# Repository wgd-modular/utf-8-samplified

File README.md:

# utf-8-samplified

An Arduino nano sample based 8-channel drum module for the eurorack format.

For more information on the project take a look into the [wiki](https://github.com/wgd-modular/utf-8-samplified/wiki)!

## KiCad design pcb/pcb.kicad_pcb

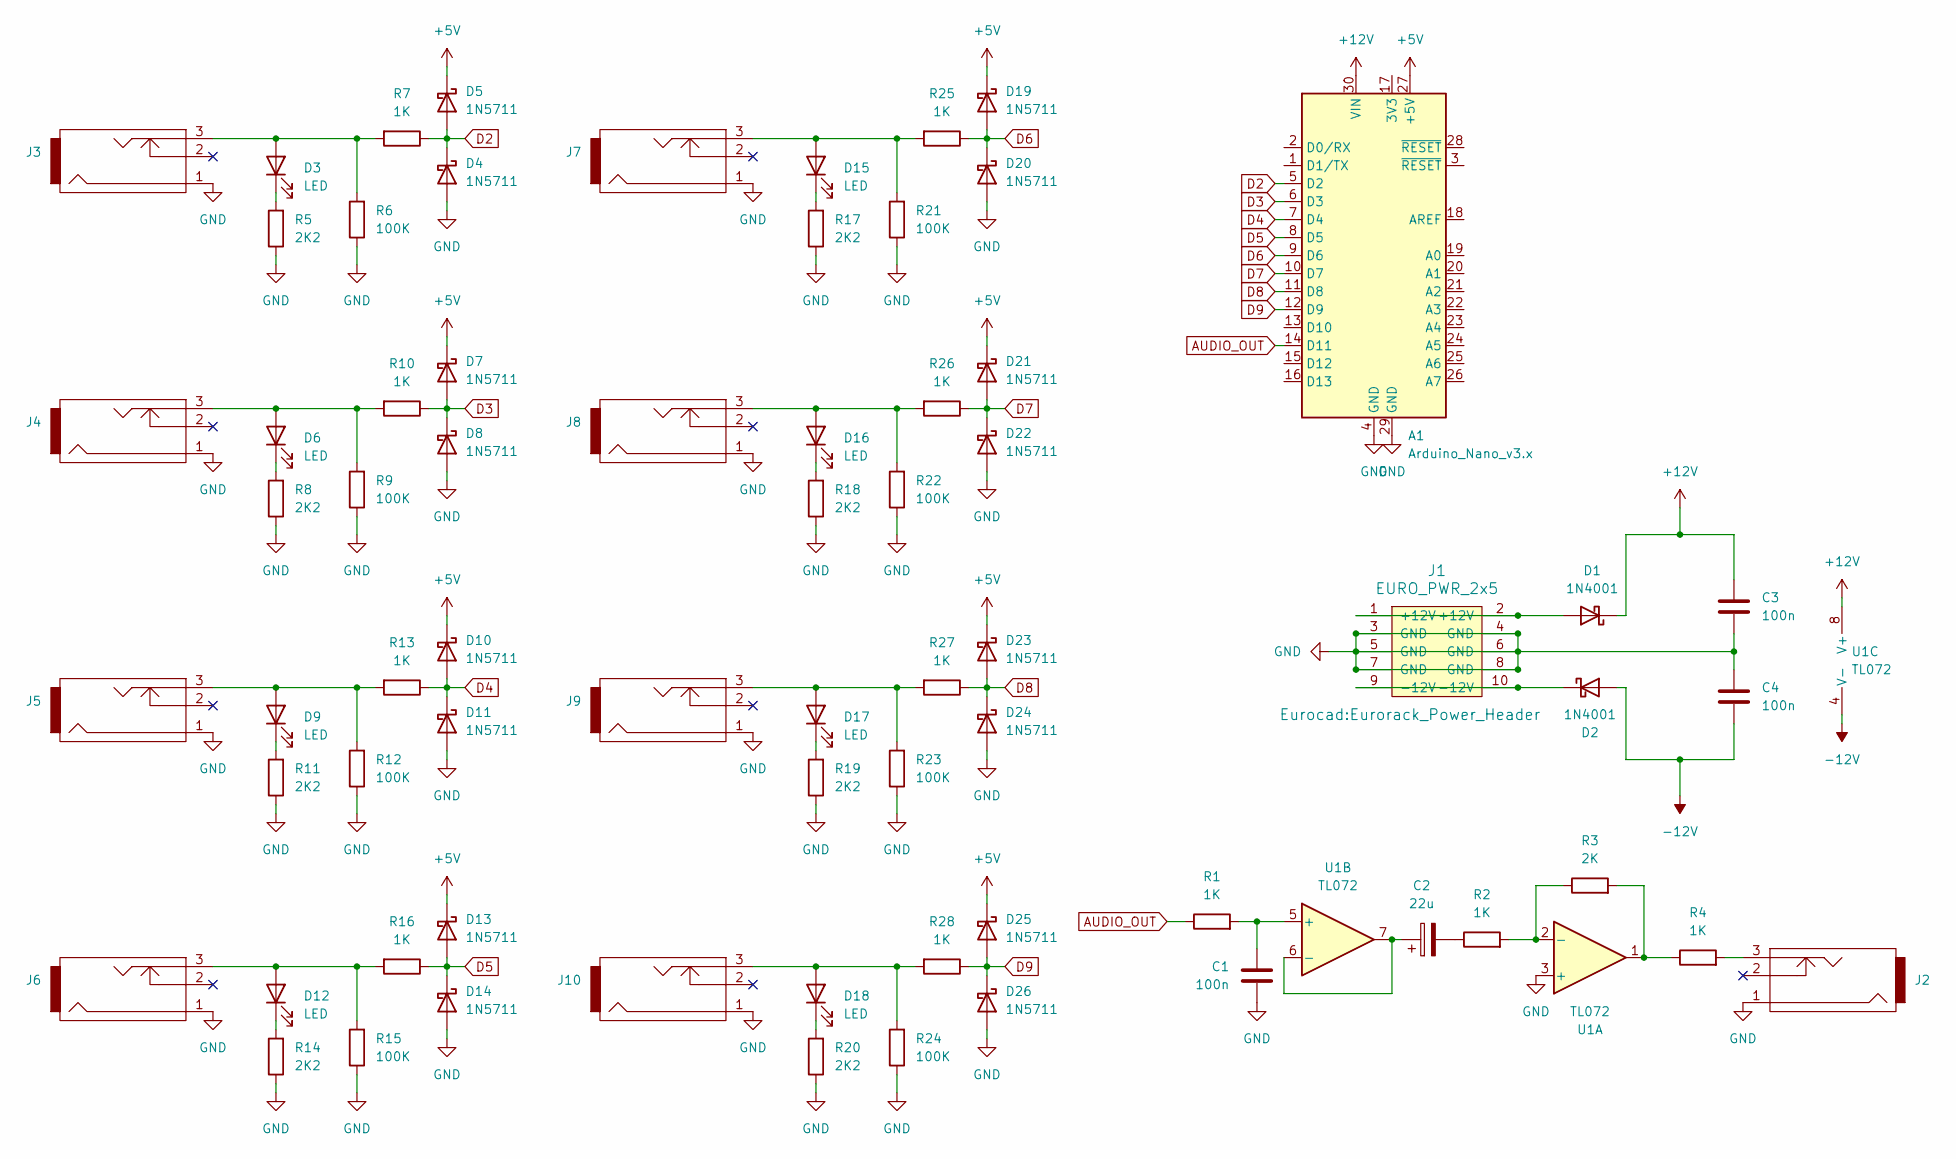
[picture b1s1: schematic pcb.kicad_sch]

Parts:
A1: Arduino_Nano_v3.x; Arduino_Nano
C1, C3, C4: 100n; C_Rect_L7.2mm_W3.0mm_P5.00mm_FKS2_FKP2_MKS2_MKP2
C2: 22u; CP_Radial_D5.0mm_P2.50mm
D1, D2: 1N4001; D_DO-41_SOD81_P10.16mm_Horizontal
D3, D6, D9, D12, D15, D16, D17, D18: LED; LED_D3.0mm
D4, D5, D7, D8, D10, D11, D13, D14, D19, D20, D21, D22, D23, D24, D25, D26: 1N5711; D_DO-35_SOD27_P7.62mm_Horizontal
J1: EURO_PWR_2x5; Eurorack_Power_Header
J2, J3, J4, J5, J6, J7, J8, J9, J10: PJ301M-12
R1, R2, R4, R7, R10, R13, R16, R25, R26, R27, R28: 1K; R_Axial_DIN0207_L6.3mm_D2.5mm_P7.62mm_Horizontal
R3: 2K; R_Axial_DIN0207_L6.3mm_D2.5mm_P7.62mm_Horizontal
R5, R8, R11, R14, R17, R18, R19, R20: 2K2; R_Axial_DIN0207_L6.3mm_D2.5mm_P7.62mm_Horizontal
R6, R9, R12, R15, R21, R22, R23, R24: 100K; R_Axial_DIN0207_L6.3mm_D2.5mm_P7.62mm_Horizontal
U1: TL072; DIP-8_W7.62mm

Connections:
+5V: A1.27 (+5V), D5.1 (K), D7.1 (K), D10.1 (K), D13.1 (K), D19.1 (K), D21.1 (K), D23.1 (K), D25.1 (K)
+12V: A1.30 (VIN), C3.1, D1.1 (K), U1.8 (V+)
-12V: C4.2, D2.2 (A), U1.4 (V-)
AUDIO_OUT: A1.14 (D11), R1.1
D2: A1.5 (D2), D4.1 (K), D5.2 (A), R7.1
D3: A1.6 (D3), D7.2 (A), D8.1 (K), R10.1
D4: A1.7 (D4), D10.2 (A), D11.1 (K), R13.1
D5: A1.8 (D5), D13.2 (A), D14.1 (K), R16.1
D6: A1.9 (D6), D19.2 (A), D20.1 (K), R25.1
D7: A1.10 (D7), D21.2 (A), D22.1 (K), R26.1
D8: A1.11 (D8), D23.2 (A), D24.1 (K), R27.1
D9: A1.12 (D9), D25.2 (A), D26.1 (K), R28.1
GND: A1.4 (GND), A1.29 (GND), C1.2, C3.2, C4.1, D4.2 (A), D8.2 (A), D11.2 (A), D14.2 (A), D20.2 (A), D22.2 (A), D24.2 (A), D26.2 (A), J1.3 (GND), J1.4 (GND), J1.5 (GND), J1.6 (GND), J1.7 (GND), J1.8 (GND), J2.1, J3.1, J4.1, J5.1, J6.1, J7.1, J8.1, J9.1, J10.1, R5.1, R6.1, R8.1, R9.1, R11.1, R12.1, R14.1, R15.1, R17.1, R18.1, R19.1, R20.1, R21.1, R22.1, R23.1, R24.1, U1.3 (+)
unnamed: C2.2, R2.1
unnamed: D1.2 (A), J1.1 (+12V), J1.2 (+12V)
unnamed: D2.1 (K), J1.9 (-12V), J1.10 (-12V)
unnamed: D3.2 (A), J3.3, R6.2, R7.2
unnamed: D3.1 (K), R5.2
unnamed: D6.2 (A), J4.3, R9.2, R10.2
unnamed: D6.1 (K), R8.2
unnamed: D9.2 (A), J5.3, R12.2, R13.2
unnamed: D9.1 (K), R11.2
unnamed: D12.2 (A), J6.3, R15.2, R16.2
unnamed: D12.1 (K), R14.2
unnamed: D15.2 (A), J7.3, R21.2, R25.2
unnamed: D15.1 (K), R17.2
unnamed: D16.2 (A), J8.3, R22.2, R26.2
unnamed: D16.1 (K), R18.2
unnamed: D17.2 (A), J9.3, R23.2, R27.2
unnamed: D17.1 (K), R19.2
unnamed: D18.2 (A), J10.3, R24.2, R28.2
unnamed: D18.1 (K), R20.2
unnamed: J2.3, R4.2
unnamed: R3.2, R4.1, U1.1
unnamed: R2.2, R3.1, U1.2 (-)
unnamed: C1.1, R1.2, U1.5 (+)
unnamed: C2.1, U1.6 (-), U1.7

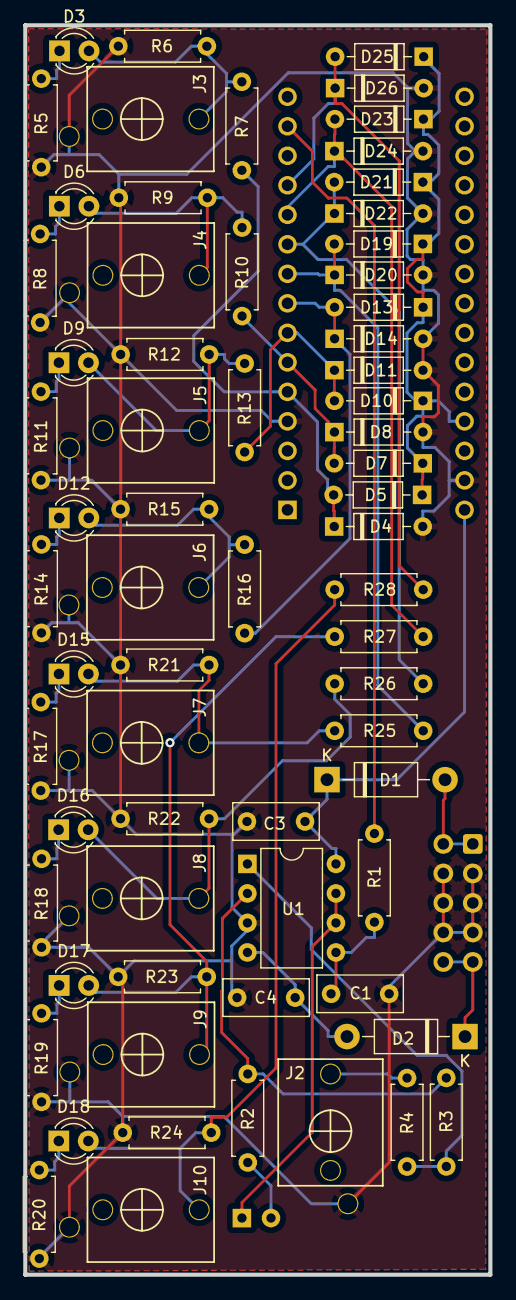
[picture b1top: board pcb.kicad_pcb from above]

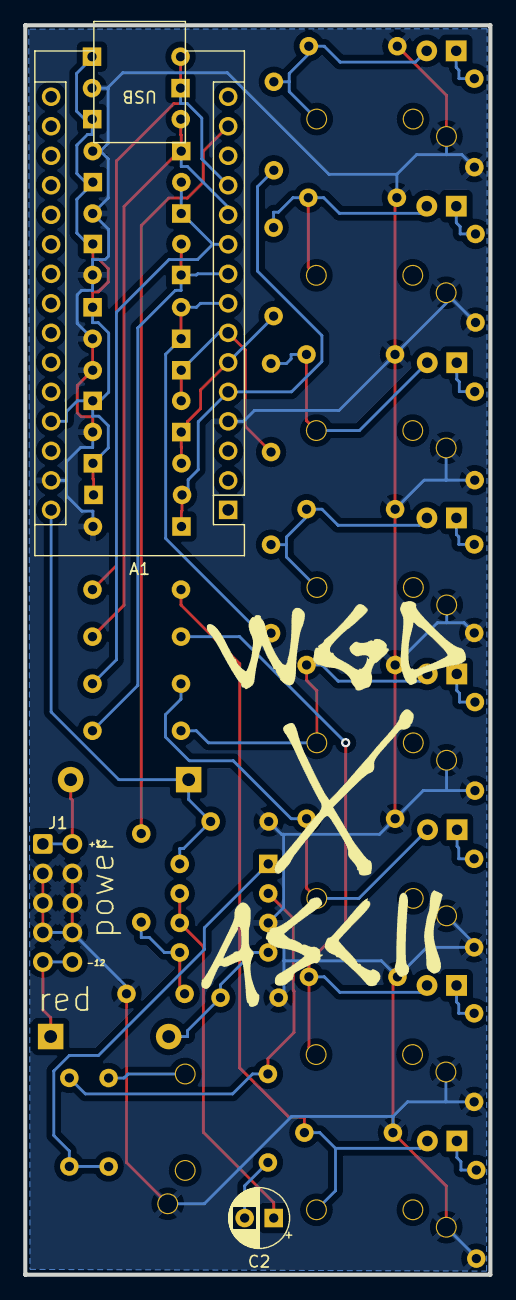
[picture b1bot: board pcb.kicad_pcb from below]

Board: 2 copper layers, 40.0 x 107.5 mm, 70 parts (3 on the bottom side), 37 nets.

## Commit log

2024-01-22 Add schematic, first panel design
2024-01-22 Fix panel labels
2024-01-22 Finish pcb
2024-02-09 Add firmware
2024-02-15 Rename dspD8_triggered.ino to firmware.ino
2024-03-20 Rename firmware/drum_samples.h to firmware/standard/drum_samples.h
2024-03-20 Rename firmware/firmware.ino to firmware/standard/firmware.ino
2024-03-20 Rename firmware.ino to standard.ino
2024-03-20 Add Mattel set
2025-02-02 Add: initial 808 kit test Add: the wav2c.py script with notes about batch processing for this application Add: jungle. Add: beatbox. its all too hight
    Fix: jungle sample lengths in main
    Fix: beatbox sample lengths in main
    Fix: 808 sample lengths in main
    Fix: move sample length out of ino, adjust arbitrary pitch in ino to constant, resample
2025-03-28 Add: initial 808 kit test (#2)
2025-04-02 Fix: pitch correction down. they were all a bit too high :)
2025-04-02 Fix: bass drum was now too deep. pull back bass 11 pts, the rest 2.
2025-04-02 Fix: crush commits
2025-04-02 Add: line for size of array
2025-04-02 Fix: newline with fout.write
2025-04-03 And redo the fixes. (#6)
    * Fix: crush commits
    * Add: line for size of array
    * Fix: newline with fout.write
2025-04-04 Fix: clicks
2025-04-04 Fix: clicks (#7)
2025-04-05 Add: initial 808 kit test (#2) And redo the fixes. (#6) * Fix: crush commits * Add: line for size of array * Fix: newline with fout.write Fix: clicks (#7) Fix: make the options easier to use on cli A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
2025-04-05 Add: dilectro kit. cli usage tips in wav2c. fixes for divergent branches
2025-04-05 Fix: add normalize
2025-04-05 Add: I store wave files in the repo while working. exclude them.
2025-04-05 Add: cavetechno. badass.
2025-04-05 Shift: add tone.
2025-04-06 Ok. pull first, double check, add badass techno kit (#9)
    * Add: dilectro kit. cli usage tips in wav2c. fixes for divergent branches
    * Fix: add normalize
    * Add: I store wave files in the repo while working. exclude them.
    * Add: cavetechno. badass.
    * Shift: add tone.
